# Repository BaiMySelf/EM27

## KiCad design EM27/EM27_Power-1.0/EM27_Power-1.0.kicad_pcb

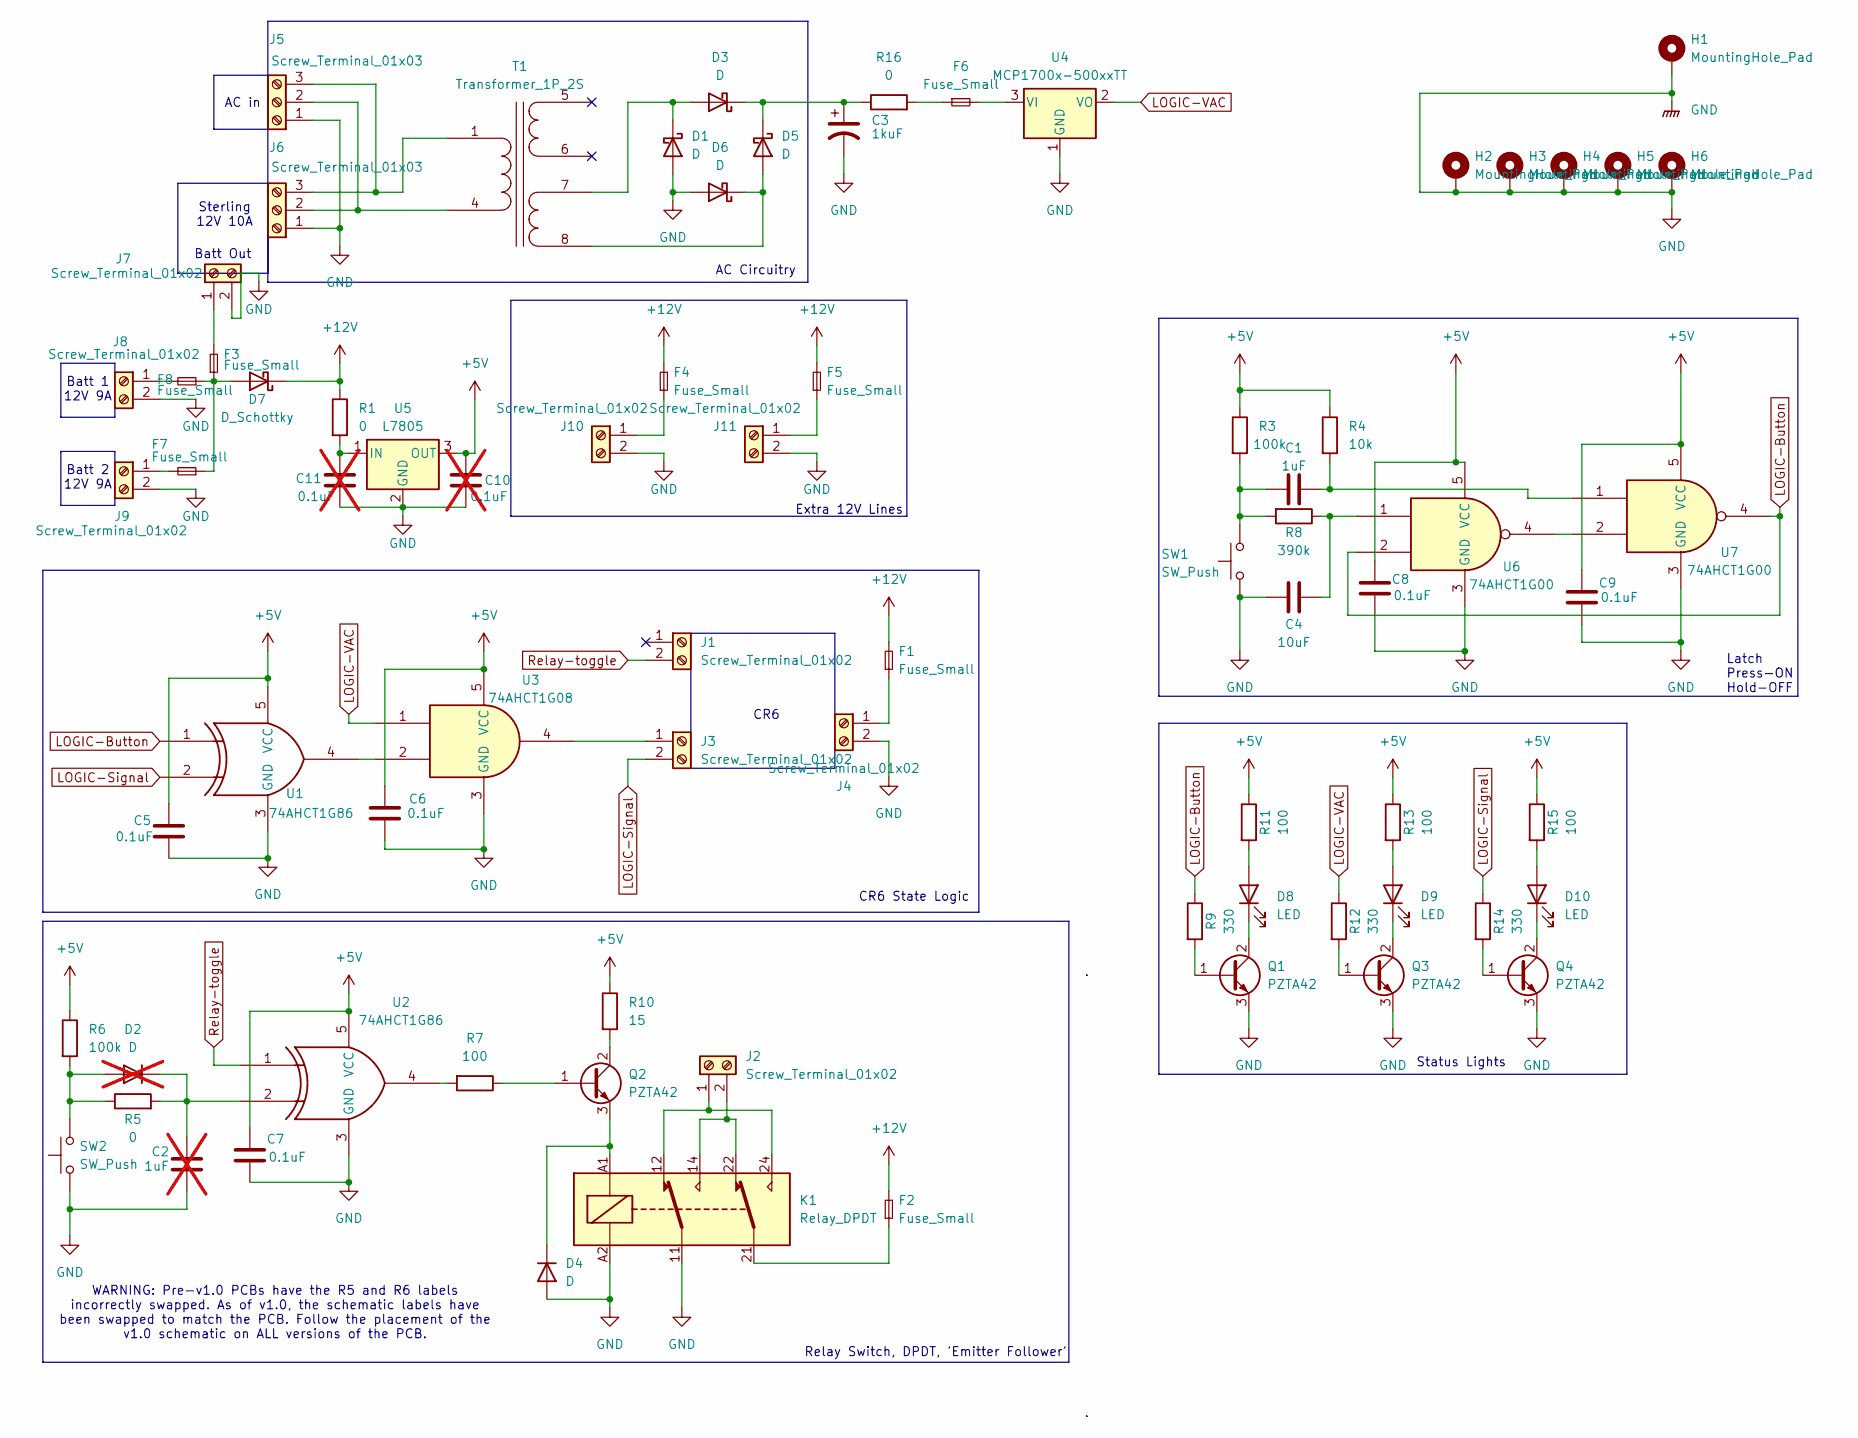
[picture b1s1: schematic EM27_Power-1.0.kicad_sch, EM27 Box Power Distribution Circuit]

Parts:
C1: 1uF; C_0805_2012Metric_Pad1.18x1.45mm_HandSolder
C2: 1uF; C_0805_2012Metric_Pad1.18x1.45mm_HandSolder; not fitted
C3: 1kuF; CP_Radial_D13.0mm_P5.00mm
C4: 10uF; C_0805_2012Metric_Pad1.18x1.45mm_HandSolder
C5, C6, C7, C8, C9: 0.1uF; C_0805_2012Metric_Pad1.18x1.45mm_HandSolder
C10, C11: 0.1uF; C_0805_2012Metric_Pad1.18x1.45mm_HandSolder; not fitted
D1, D3, D5, D6: D; D_DO-41_SOD81_P10.16mm_Horizontal
D2: D; D_SMB_Handsoldering; not fitted
D4: D; D_SMB_Handsoldering
D7: D_Schottky; D_SMB_Handsoldering
D8, D9, D10: LED; LED_D5.0mm
F1, F2, F3, F4, F5, F6, F7, F8: Fuse_Small; FUSE_5x20
H1, H2, H3, H4, H5, H6: MountingHole_Pad; MountingHole_3.2mm_M3_Pad
J1, J2, J3, J4, J7, J8, J9, J10, J11: Screw_Terminal_01x02; KobiConn_5.08mm-2pos-35deg_screwterminal
J5, J6: Screw_Terminal_01x03; Molex_Barrier_Term_Block-8.26mm-3pos
K1: Relay_DPDT; J114FL2CS85VDC41
Q1, Q2, Q3, Q4: PZTA42; SOT-223-3_TabPin2
R1, R5, R16: 0; R_0805_2012Metric_Pad1.20x1.40mm_HandSolder
R3, R6: 100k; R_0805_2012Metric_Pad1.20x1.40mm_HandSolder
R4: 10k; R_0805_2012Metric_Pad1.20x1.40mm_HandSolder
R7, R11, R13, R15: 100; R_0805_2012Metric_Pad1.20x1.40mm_HandSolder
R8: 390k; R_0805_2012Metric_Pad1.20x1.40mm_HandSolder
R9, R12, R14: 330; R_0805_2012Metric_Pad1.20x1.40mm_HandSolder
R10: 15; R_0805_2012Metric_Pad1.20x1.40mm_HandSolder
SW1, SW2: SW_Push; KobiConn_5.08mm-2pos-35deg_screwterminal
T1: Transformer_1P_2S; F12-090-C2
U1, U2: 74AHCT1G86; SOT-23-5_HandSoldering
U3: 74AHCT1G08; SOT-23-5_HandSoldering
U4: MCP1700x-500xxTT; SOT-23
U5: L7805; TO-263-3_TabPin2
U6, U7: 74AHCT1G00; SOT-23-5_HandSoldering

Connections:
+5V: C5.1, C6.1, C7.1, C8.1, C9.1, C10.1, R3.1, R4.1, R6.1, R10.1, R11.1, R13.1, R15.1, U1.5 (VCC), U2.5 (VCC), U3.5 (VCC), U5.3 (OUT), U6.5 (VCC), U7.5 (VCC)
+12V: D7.1 (K), F1.2, F2.2, F4.2, F5.2, R1.1
GND: C2.2, C3.2, C4.2, C5.2, C6.2, C7.2, C8.2, C9.2, C10.2, C11.2, D1.2 (A), D4.2 (A), D6.2 (A), H1.1, H2.1, H3.1, H4.1, H5.1, H6.1, J4.2, J5.1, J6.1, J7.2, J8.2, J9.2, J10.2, J11.2, K1.11, K1.A2, Q1.3 (E), Q3.3 (E), Q4.3 (E), SW1.1, SW2.1, U1.3 (GND), U2.3 (GND), U3.3 (GND), U4.1 (GND), U5.2 (GND), U6.3 (GND), U7.3 (GND)
LOGIC-Button: R9.1, U1.1, U6.2, U7.4
LOGIC-Signal: J3.2, R14.1, U1.2
LOGIC-VAC: R12.1, U3.1, U4.2 (VO)
unnamed: C1.1, R4.2, U7.1
unnamed: C1.2, R3.2, R8.2, SW1.2
unnamed: C4.1, R8.1, U6.1
unnamed: D1.1 (K), D3.2 (A), T1.7 (SC)
unnamed: D2.2 (A), R5.1, R6.2, SW2.2
unnamed: C2.1, D2.1 (K), R5.2, U2.2
unnamed: C3.1, D3.1 (K), D5.1 (K), R16.1
unnamed: D4.1 (K), K1.A1, Q2.3 (E)
unnamed: D5.2 (A), D6.1 (K), T1.8 (SD)
unnamed: D7.2 (A), F3.1, F7.1, F8.1
unnamed: D8.2 (A), R11.2
unnamed: D8.1 (K), Q1.2 (C)
unnamed: D9.2 (A), R13.2
unnamed: D9.1 (K), Q3.2 (C)
unnamed: D10.2 (A), R15.2
unnamed: D10.1 (K), Q4.2 (C)
unnamed: F2.1, K1.21
unnamed: F6.1, R16.2
unnamed: J2.1, K1.12, K1.24
unnamed: J2.2, K1.14, K1.22
unnamed: J3.1, U3.4
unnamed: F1.1, J4.1
unnamed: J5.2, J6.2, T1.4 (AB)
unnamed: J5.3, J6.3, T1.1 (AA)
unnamed: F3.2, J7.1
unnamed: F8.2, J8.1
unnamed: F7.2, J9.1
unnamed: F4.1, J10.1
unnamed: F5.1, J11.1
unnamed: Q1.1 (B), R9.2
unnamed: Q2.1 (B), R7.1
unnamed: Q2.2 (C), R10.2
unnamed: Q3.1 (B), R12.2
unnamed: Q4.1 (B), R14.2
unnamed: R7.2, U2.4
unnamed: U1.4, U3.2
unnamed: F6.2, U4.3 (VI)
unnamed: C11.1, R1.2, U5.1 (IN)
unnamed: U6.4, U7.2
Relay-toggle: J1.2, U2.1

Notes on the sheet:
Sterling 12V 10A
Status Lights
Batt 2 12V 9A
Extra 12V Lines
CR6
AC Circuitry
WARNING: Pre-v1.0 PCBs have the R5 and R6 labels incorrectly swapped. As of v1.0, the schematic labels have been swapped to match the PCB. Follow the placement of the v1.0 schematic on ALL versions of the PCB.
Batt 1 12V 9A
Batt Out
CR6 State Logic
Latch Press-ON Hold-OFF
AC in
Relay Switch, DPDT, 'Emitter Follower'

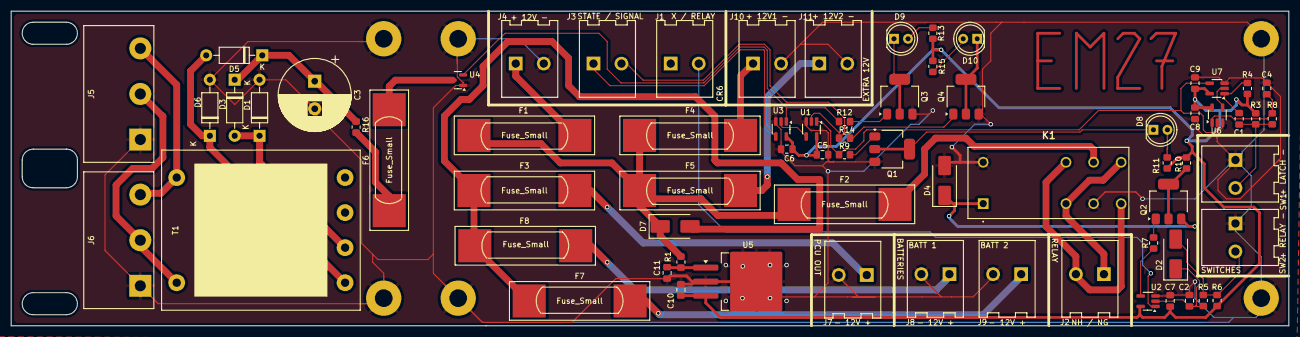
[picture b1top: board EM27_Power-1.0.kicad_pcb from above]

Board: 2 copper layers, 231.5 x 57.0 mm, 76 parts (0 on the bottom side), 46 nets.

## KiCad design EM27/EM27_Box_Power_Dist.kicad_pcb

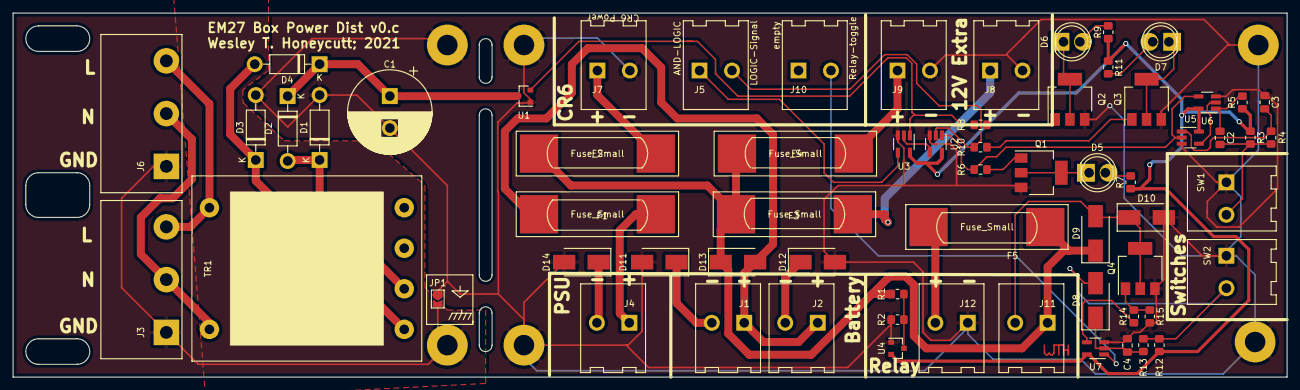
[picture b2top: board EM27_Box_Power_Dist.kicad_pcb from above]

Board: 2 copper layers, 199.5 x 57.0 mm, 71 parts (0 on the bottom side), 43 nets.

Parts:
C1: 1kF; CP_Radial_D13.0mm_P5.00mm
C2, C3, C4: 1uF; C_0805_2012Metric_Pad1.18x1.45mm_HandSolder
D1, D2, D3, D4: 1N4007; D_DO-41_SOD81_P10.16mm_Horizontal
D5, D6, D7: LED; LED_D5.0mm
D8, D9, D10: 1n4002; D_SMB_Handsoldering
D11, D12, D13, D14: D_Schottky; D_SMB_Handsoldering
F1, F2, F3, F4, F5: Fuse_Small; FUSE_5x20
H1, H2, H3, H4, H5, H6: MountingHole_Pad; MountingHole_3.2mm_M3_Pad
J1, J2, J4, J5, J7, J8, J9, J10, J11, J12: Screw_Terminal_01x02; KobiConn_5.08mm-2pos-35deg_screwterminal
J3, J6: Screw_Terminal_01x03; Molex_Barrier_Term_Block-8.26mm-3pos
JP1: Jumper_NO_Small; SolderJumper-2_P1.3mm_Open_TrianglePad1.0x1.5mm
Q1, Q2, Q3, Q4: PZT3904; SOT-223-3_TabPin2
R1: 15k; R_0805_2012Metric_Pad1.20x1.40mm_HandSolder
R2, R7, R9, R11: 10k; R_0805_2012Metric_Pad1.20x1.40mm_HandSolder
R3, R5, R12: 100k; R_0805_2012Metric_Pad1.20x1.40mm_HandSolder
R4, R13: 5M; R_0805_2012Metric_Pad1.20x1.40mm_HandSolder
R6, R8, R10, R14, R15: 0R; R_0805_2012Metric_Pad1.20x1.40mm_HandSolder
SW1, SW2: SW_Push; KobiConn_5.08mm-2pos-35deg_screwterminal
TR1: F12-090-C2_Transformer; F12-090-C2
U1, U4: MCP1700-5002E_SOT23; SOT-23
U2, U7: 74AHCT1G86; SOT-23-5_HandSoldering
U3: 74AHCT1G08; SOT-23-5_HandSoldering
U5, U6: 74AHCT1G00; SOT-23-5_HandSoldering

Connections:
+5V: R3.1, R5.1, R7.1, R9.1, R11.1, R12.1, U2.5, U3.5, U4.2, U5.5, U6.5, U7.5
+12V: D9.1, D13.1, F2.1, F3.1, F4.1, F5.1, J11.1, R1.1
GND: C1.2, C3.1, C4.1, D1.2, D3.2, D10.2, D11.2, D12.2, D14.2, H1.1, H2.1, H3.1, H4.1, H6.1, J7.2, J8.2, J9.2, J12.1, JP1.1, Q1.3, Q2.3, Q3.3, Q4.3, R2.2, R15.2, SW1.1, SW2.1, U1.1, U2.3, U3.3, U4.1, U5.3, U6.3, U7.3
GNDPWR: H5.1, J3.1, J6.1, JP1.2
LOGIC-Button: R6.2, U2.1, U5.2, U6.4
LOGIC-Signal: J5.2, R10.2, U2.2
LOGIC-VAC: R8.2, U1.2, U3.1
unnamed: C1.1, D2.1, D4.1, U1.3
unnamed: C2.1, R5.2, U6.1
unnamed: C2.2, R3.2, R4.1, SW1.2
unnamed: C3.2, R4.2, U5.1
unnamed: C4.2, D8.1, R13.2, U7.2
unnamed: D1.1, D2.2, TR1.7
unnamed: D3.1, D4.2, TR1.8
unnamed: D5.1, Q1.2
unnamed: D5.2, R7.2
unnamed: D6.1, Q2.2
unnamed: D6.2, R9.2
unnamed: D7.1, Q3.2
unnamed: D7.2, R11.2
unnamed: D8.2, R12.2, R13.1, SW2.2
unnamed: D9.2, D10.1, J11.2, Q4.2
unnamed: D11.1, J1.2
unnamed: D12.1, J2.2
unnamed: D13.2, F1.2, J1.1, J2.1
unnamed: D14.1, J4.2
unnamed: F1.1, J4.1
unnamed: F2.2, J7.1
unnamed: F3.2, J8.1
unnamed: F4.2, J9.1
unnamed: F5.2, J12.2
unnamed: J3.2, J6.2, TR1.4
unnamed: J3.3, J6.3, TR1.1
unnamed: J5.1, U3.4
unnamed: Q1.1, R6.1
unnamed: Q2.1, R8.1
unnamed: Q3.1, R10.1
unnamed: Q4.1, R14.2, R15.1
unnamed: R1.2, R2.1, U4.3
unnamed: R14.1, U7.4
unnamed: U2.4, U3.2
unnamed: U5.4, U6.2
Relay-toggle: J10.2, U7.1

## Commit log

2025-05-21 EM27 Files 05/21/25
2025-06-09 Latest EM27 PCB design
2025-08-06 EM27 v1.0
    Schematic and PCB updated to match working PCB.
